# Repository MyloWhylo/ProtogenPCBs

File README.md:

# ProtogenPCBs
Repository for ProtoPico and BackpackController

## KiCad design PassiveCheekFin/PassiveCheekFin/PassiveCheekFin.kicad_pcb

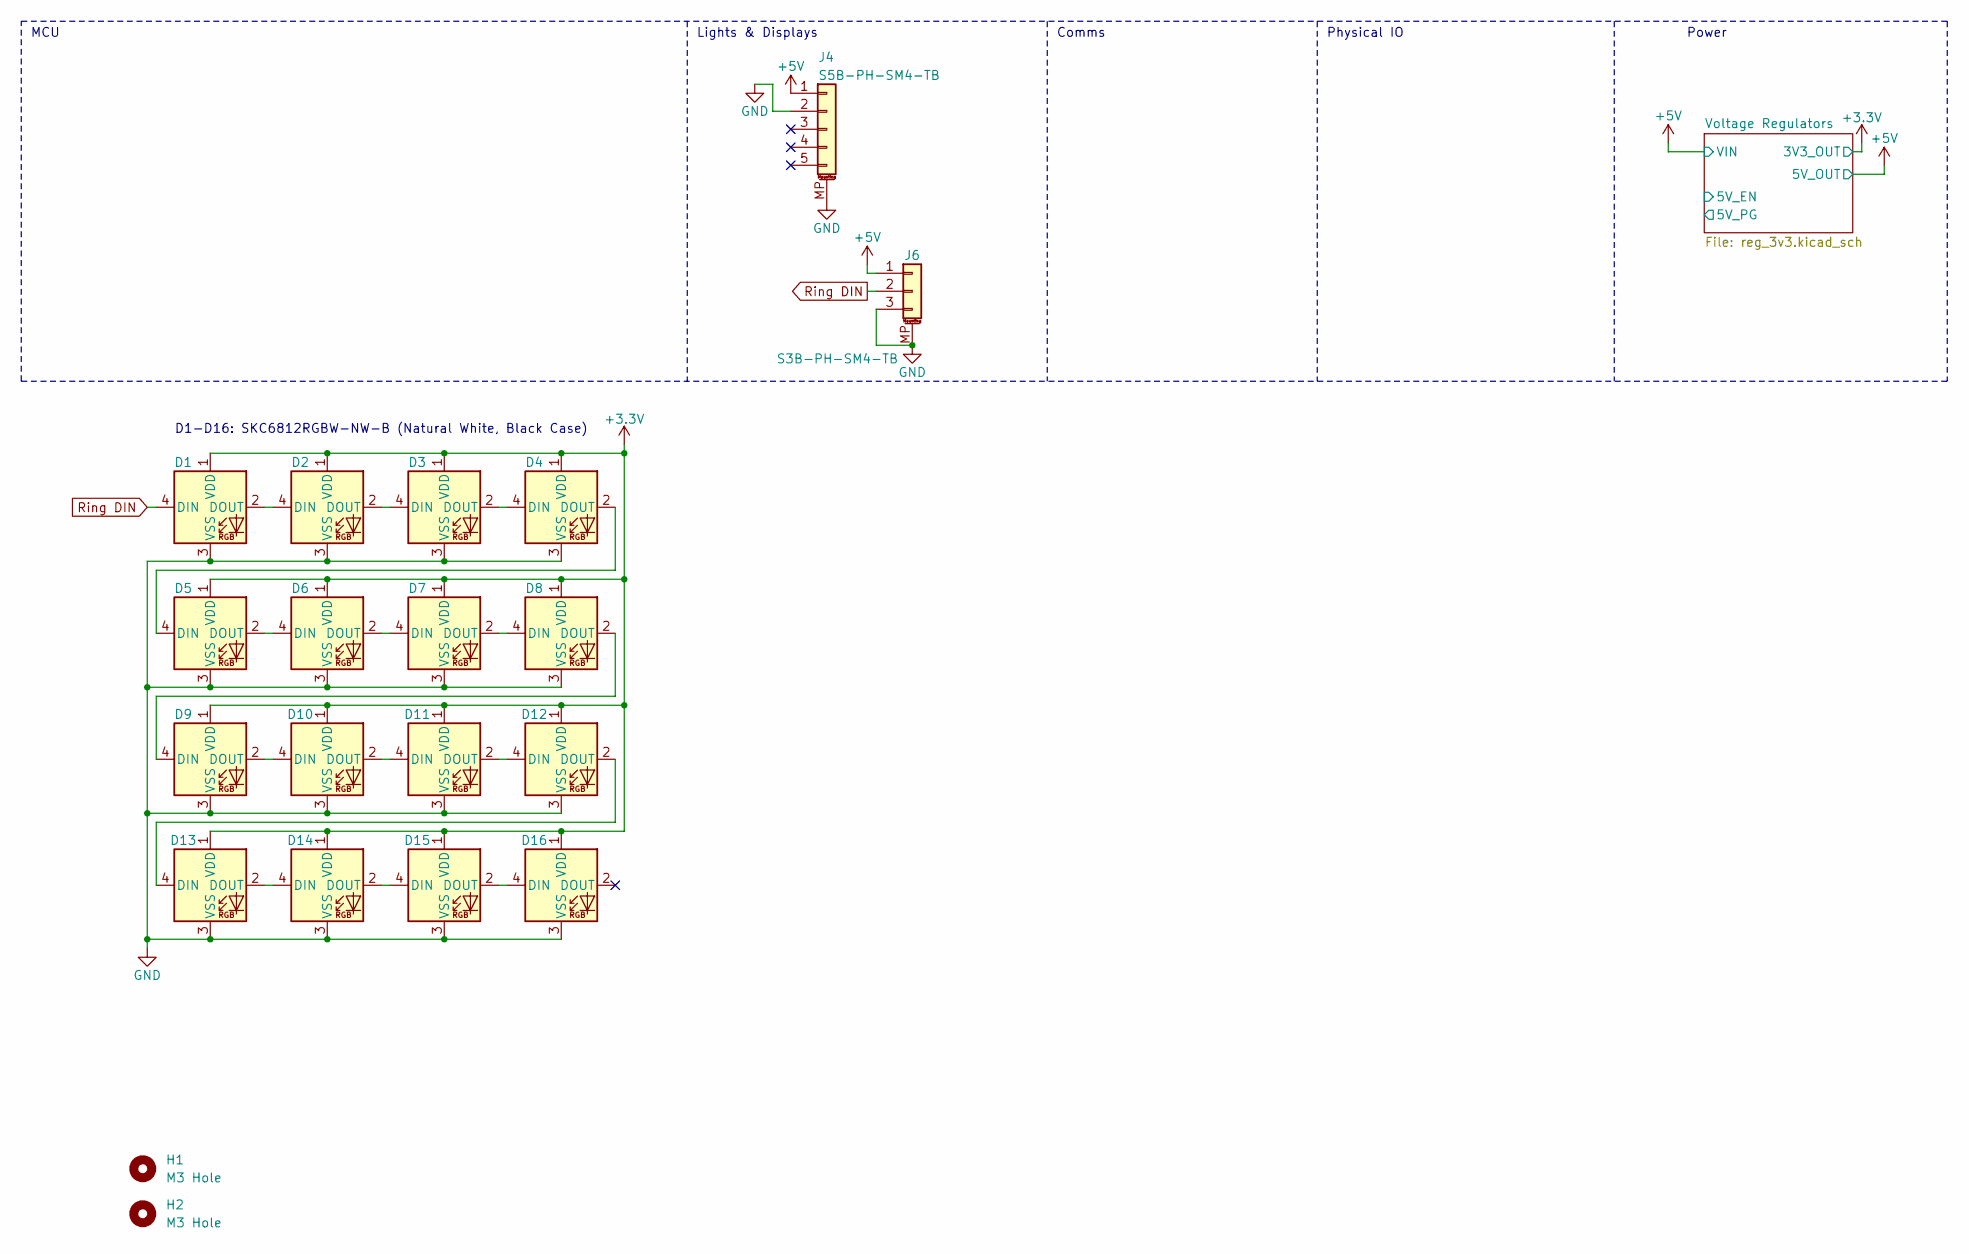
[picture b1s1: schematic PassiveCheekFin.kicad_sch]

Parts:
D1, D2, D3, D4, D5, D6, D7, D8, D9, D10, D11, D12, D13, D14, D15, D16: SKC6812RGBW-NW-B; LED_WS2812B_PLCC4_5.0x5.0mm_P3.2mm
H1, H2: M3 Hole; MountingHole_3.2mm_M3_ISO14580
J4: S5B-PH-SM4-TB; JST_PH_S5B-PH-SM4-TB_1x05-1MP_P2.00mm_Horizontal
J6: S3B-PH-SM4-TB; JST_PH_S3B-PH-SM4-TB_1x03-1MP_P2.00mm_Horizontal

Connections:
+3.3V: D1.1 (VDD), D2.1 (VDD), D3.1 (VDD), D4.1 (VDD), D5.1 (VDD), D6.1 (VDD), D7.1 (VDD), D8.1 (VDD), D9.1 (VDD), D10.1 (VDD), D11.1 (VDD), D12.1 (VDD), D13.1 (VDD), D14.1 (VDD), D15.1 (VDD), D16.1 (VDD); also elsewhere on the board
+5V: J4.1, J6.1; also elsewhere on the board
GND: D1.3 (VSS), D2.3 (VSS), D3.3 (VSS), D4.3 (VSS), D5.3 (VSS), D6.3 (VSS), D7.3 (VSS), D8.3 (VSS), D9.3 (VSS), D10.3 (VSS), D11.3 (VSS), D12.3 (VSS), D13.3 (VSS), D14.3 (VSS), D15.3 (VSS), D16.3 (VSS), J4.2, J4.MP (MountPin), J6.3, J6.MP (MountPin); also elsewhere on the board
unnamed: D1.2 (DOUT), D2.4 (DIN)
unnamed: D2.2 (DOUT), D3.4 (DIN)
unnamed: D3.2 (DOUT), D4.4 (DIN)
unnamed: D4.2 (DOUT), D5.4 (DIN)
unnamed: D5.2 (DOUT), D6.4 (DIN)
unnamed: D6.2 (DOUT), D7.4 (DIN)
unnamed: D7.2 (DOUT), D8.4 (DIN)
unnamed: D8.2 (DOUT), D9.4 (DIN)
unnamed: D9.2 (DOUT), D10.4 (DIN)
unnamed: D10.2 (DOUT), D11.4 (DIN)
unnamed: D11.2 (DOUT), D12.4 (DIN)
unnamed: D12.2 (DOUT), D13.4 (DIN)
unnamed: D13.2 (DOUT), D14.4 (DIN)
unnamed: D14.2 (DOUT), D15.4 (DIN)
unnamed: D15.2 (DOUT), D16.4 (DIN)
Ring DIN: D1.4 (DIN), J6.2

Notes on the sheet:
Power
Physical IO
Comms
Lights & Displays
MCU
D1-D16: SKC6812RGBW-NW-B (Natural White, Black Case)

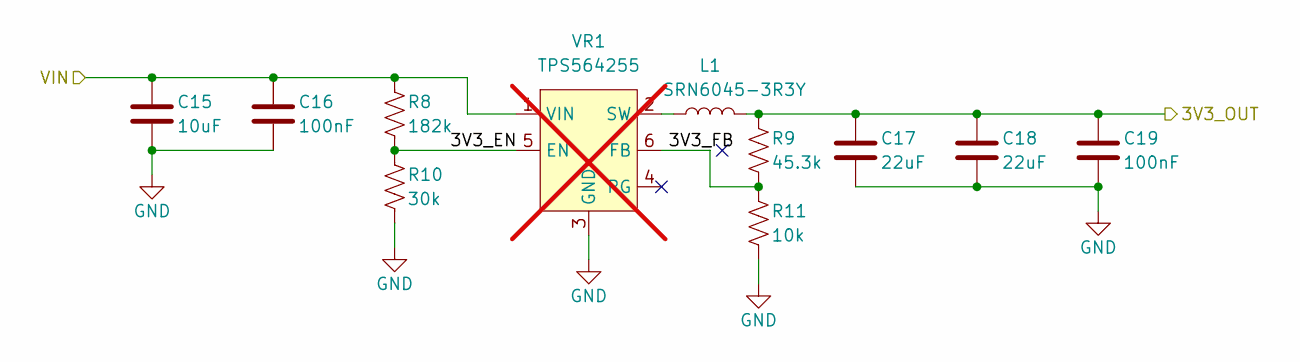
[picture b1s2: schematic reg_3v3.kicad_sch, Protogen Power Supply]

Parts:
C15: 10uF; C_0805_2012Metric
C16, C19: 100nF; C_0603_1608Metric
C17, C18: 22uF; C_0805_2012Metric
L1: SRN6045-3R3Y; L_Bourns-SRN6028
R8: 182k; R_0805_2012Metric_Pad1.20x1.40mm_HandSolder
R9: 45.3k; R_0402_1005Metric
R10: 30k; R_0805_2012Metric_Pad1.20x1.40mm_HandSolder
R11: 10k; R_0402_1005Metric
VR1: TPS564255; SOT-563; not fitted

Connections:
+3.3V: C17.1, C18.1, C19.1, L1.2, R9.1; also elsewhere on the board
+5V: C15.1, C16.1, R8.1, VR1.1 (VIN); also elsewhere on the board
/Voltage Regulators/3V3_EN: R8.2, R10.1, VR1.5 (EN)
/Voltage Regulators/3V3_FB: R9.2, R11.1, VR1.6 (FB)
GND: C15.2, C16.2, C17.2, C18.2, C19.2, R10.2, R11.2, VR1.3 (GND); also elsewhere on the board
unnamed: L1.1, VR1.2 (SW)

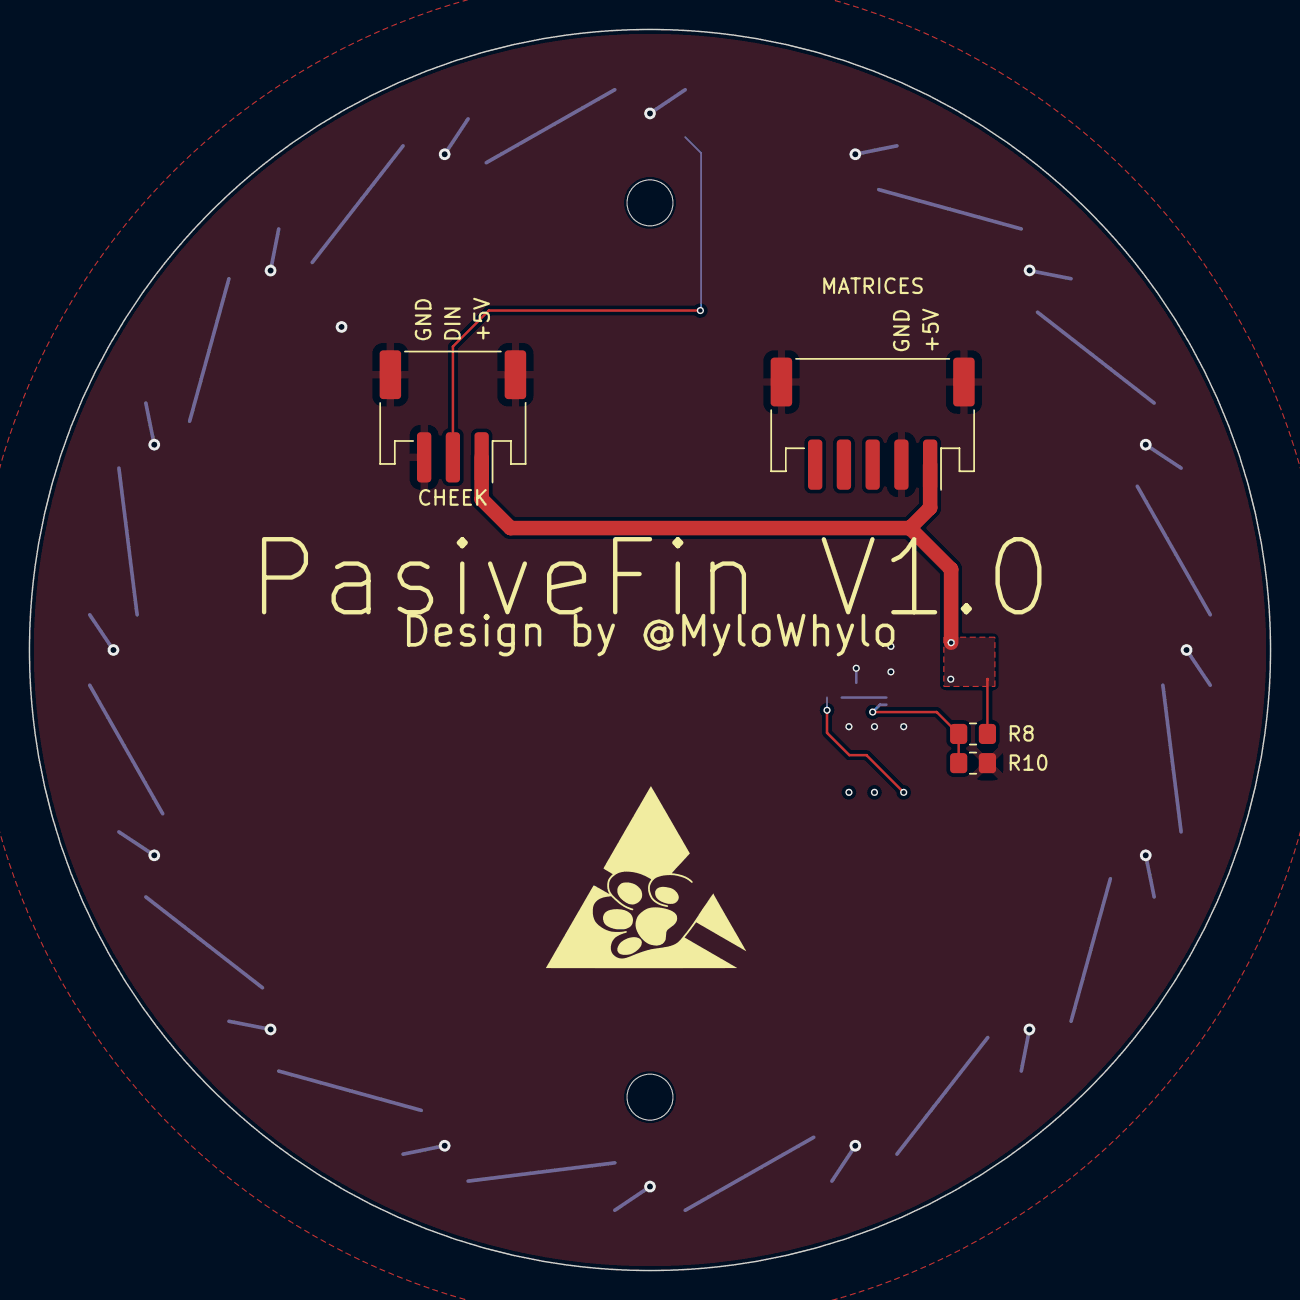
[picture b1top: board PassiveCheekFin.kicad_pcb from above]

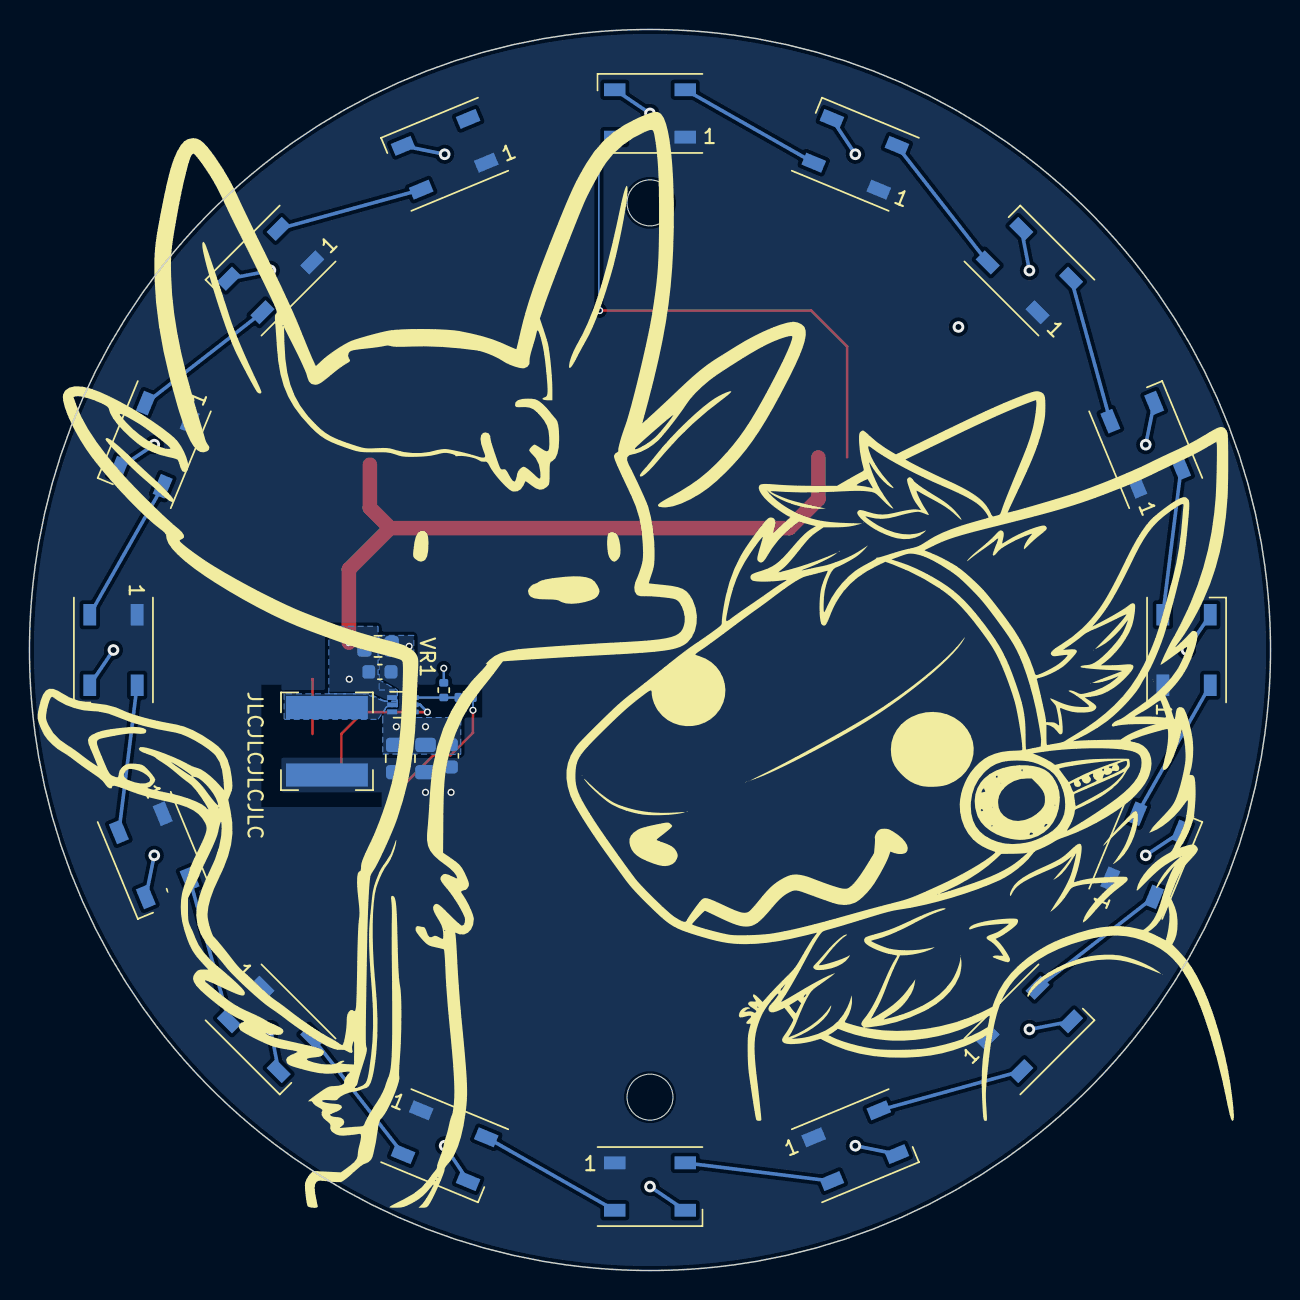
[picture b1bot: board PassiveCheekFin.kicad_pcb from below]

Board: 2 copper layers, 86.4 x 86.4 mm, 31 parts (27 on the bottom side), 22 nets.

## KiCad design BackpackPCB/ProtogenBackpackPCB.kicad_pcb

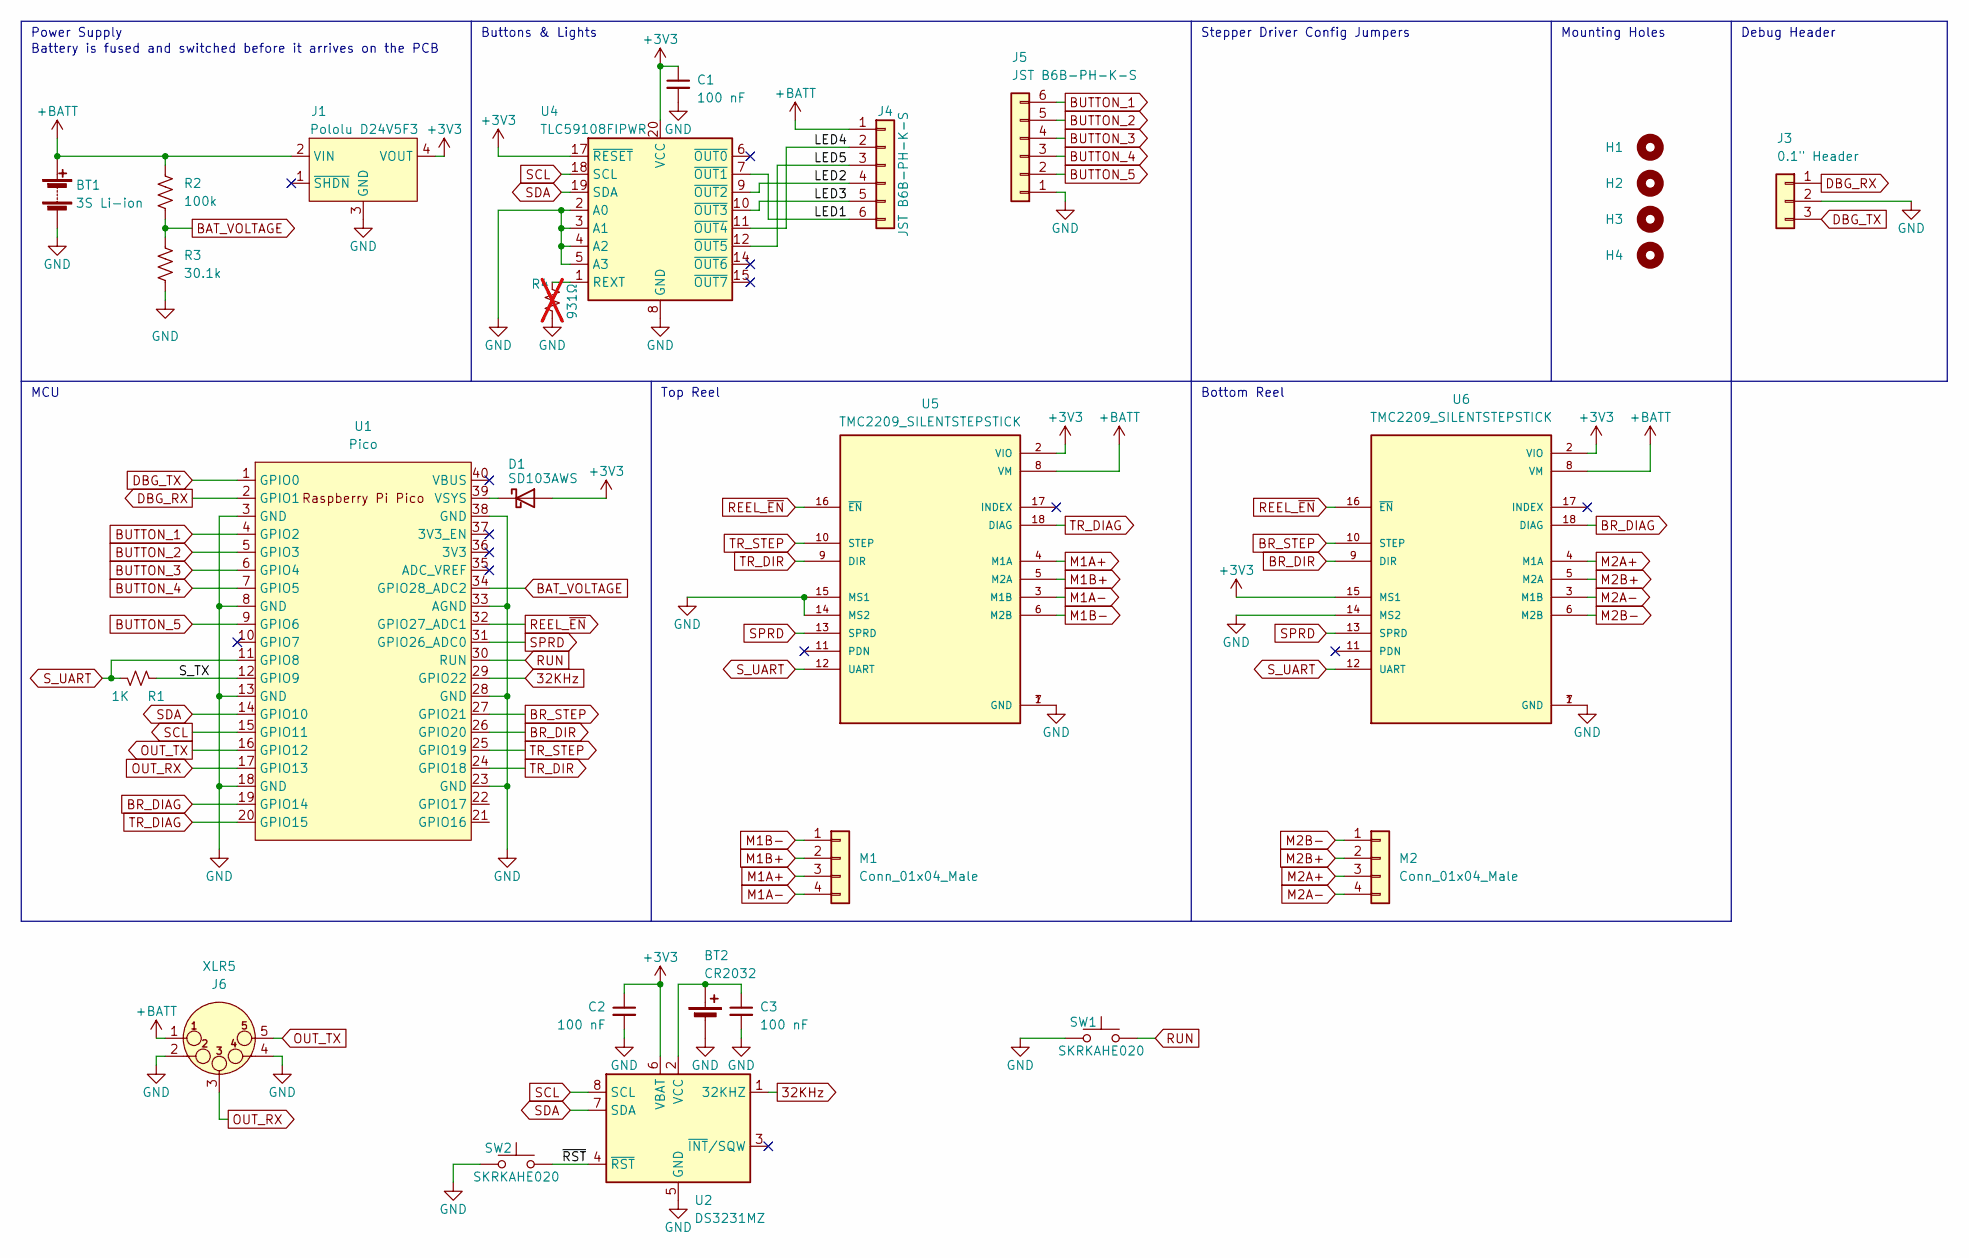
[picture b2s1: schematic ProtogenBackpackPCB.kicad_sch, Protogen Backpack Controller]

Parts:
BT1: 3S Li-ion; JST_XH_B2B-XH-AM_1x02_P2.50mm_Vertical
BT2: CR2032; BatteryHolder_Keystone_1060_1x2032
C1, C2, C3: 100 nF; C_0603_1608Metric_Pad1.08x0.95mm_HandSolder
D1: SD103AWS; D_SOD-323_HandSoldering
H1, H2, H3, H4: MountingHole_Pad; MountingHole_3.2mm_M3_ISO7380
J1: Pololu D24V5F3; Pololu_D24V5Fx
J3: 0.1" Header; PinSocket_1x03_P2.54mm_Vertical
J4, J5: JST B6B-PH-K-S; JST_PH_B6B-PH-K_1x06_P2.00mm_Vertical
J6: XLR5; JST_PH_B5B-PH-K_1x05_P2.00mm_Vertical
M1, M2: Conn_01x04_Male; JST_PH_B4B-PH-K_1x04_P2.00mm_Vertical
R1: 1K; R_0805_2012Metric_Pad1.20x1.40mm_HandSolder
R2: 100k; R_0603_1608Metric_Pad0.98x0.95mm_HandSolder
R3: 30.1k; R_0603_1608Metric_Pad0.98x0.95mm_HandSolder
R4: 931Ω; R_0402_1005Metric_Pad0.72x0.64mm_HandSolder; not fitted
SW1, SW2: SKRKAHE020; SW_Push_SPST_NO_Alps_SKRK
U1: Pico; RPi_Pico_SMD_TH
U2: DS3231MZ; SOIC-8_3.9x4.9mm_P1.27mm
U4: TLC59108FIPWR; TSSOP-20_4.4x6.5mm_P0.65mm
U5, U6: TMC2209_SILENTSTEPSTICK; MODULE_TMC2209_SILENTSTEPSTICK; PARTREV 1.20

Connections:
32KHz: U1.29 (GPIO22), U2.1 (32KHZ)
+3V3: C1.1, C2.1, D1.2 (A), J1.4 (VOUT), U2.6 (VBAT), U4.17 (~RESET), U4.20 (VCC), U5.2 (VIO), U6.2 (VIO), U6.15 (MS1)
+BATT: BT1.1 (+), J1.2 (VIN), J4.1, J6.1, R2.1, U5.8 (VM), U6.8 (VM)
/LED1: J4.6, U4.7 (~OUT1)
/LED2: J4.4, U4.9 (~OUT2)
/LED3: J4.5, U4.10 (~OUT3)
/LED4: J4.2, U4.11 (~OUT4)
/LED5: J4.3, U4.12 (~OUT5)
/S_TX: R1.2, U1.12 (GPIO9)
/~RST: SW2.2, U2.4 (~RST)
BAT_VOLTAGE: R2.2, R3.1, U1.34 (GPIO28_ADC2)
BR_DIAG: U1.19 (GPIO14), U6.18 (DIAG)
BR_DIR: U1.26 (GPIO20), U6.9 (DIR)
BR_STEP: U1.27 (GPIO21), U6.10 (STEP)
BUTTON_1: J5.6, U1.4 (GPIO2)
BUTTON_2: J5.5, U1.5 (GPIO3)
BUTTON_3: J5.4, U1.6 (GPIO4)
BUTTON_4: J5.3, U1.7 (GPIO5)
BUTTON_5: J5.2, U1.9 (GPIO6)
DBG_RX: J3.1, U1.2 (GPIO1)
DBG_TX: J3.3, U1.1 (GPIO0)
GND: BT1.2 (-), BT2.2 (-), C1.2, C2.2, C3.2, J1.3 (GND), J3.2, J5.1, J6.2, J6.4 (P3), R3.2, R4.1, SW1.1, SW2.1, U1.3 (GND), U1.8 (GND), U1.13 (GND), U1.18 (GND), U1.23 (GND), U1.28 (GND), U1.33 (AGND), U1.38 (GND), U2.5 (GND), U4.2 (A0), U4.3 (A1), U4.4 (A2), U4.5 (A3), U4.8 (GND), U4.13 (GND), U4.16 (GND), U5.1 (GND), U5.7 (GND), U5.14 (MS2), U5.15 (MS1), U6.1 (GND), U6.7 (GND), U6.14 (MS2)
M1A+: M1.3, U5.4 (M1A)
M1A-: M1.4, U5.3 (M1B)
M1B+: M1.2, U5.5 (M2A)
M1B-: M1.1, U5.6 (M2B)
M2A+: M2.3, U6.4 (M1A)
M2A-: M2.4, U6.3 (M1B)
M2B+: M2.2, U6.5 (M2A)
M2B-: M2.1, U6.6 (M2B)
unnamed: BT2.1 (+), C3.1, U2.2 (VCC)
unnamed: D1.1 (K), U1.39 (VSYS)
unnamed: R4.2, U4.1 (REXT)
OUT_RX: J6.3, U1.17 (GPIO13)
OUT_TX: J6.5, U1.16 (GPIO12)
REEL_~EN: U1.32 (GPIO27_ADC1), U5.16 (~EN), U6.16 (~EN)
RUN: SW1.2, U1.30 (RUN)
SCL: U1.15 (GPIO11), U2.8 (SCL), U4.18 (SCL)
SDA: U1.14 (GPIO10), U2.7 (SDA), U4.19 (SDA)
SPRD: U1.31 (GPIO26_ADC0), U5.13 (SPRD), U6.13 (SPRD)
S_UART: R1.1, U1.11 (GPIO8), U5.12 (UART), U6.12 (UART)
TR_DIAG: U1.20 (GPIO15), U5.18 (DIAG)
TR_DIR: U1.24 (GPIO18), U5.9 (DIR)
TR_STEP: U1.25 (GPIO19), U5.10 (STEP)

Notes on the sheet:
Battery is fused and switched before it arrives on the PCB
Stepper Driver Config Jumpers
Power Supply
Buttons & Lights
Debug Header
Top Reel
Mounting Holes
MCU
Bottom Reel

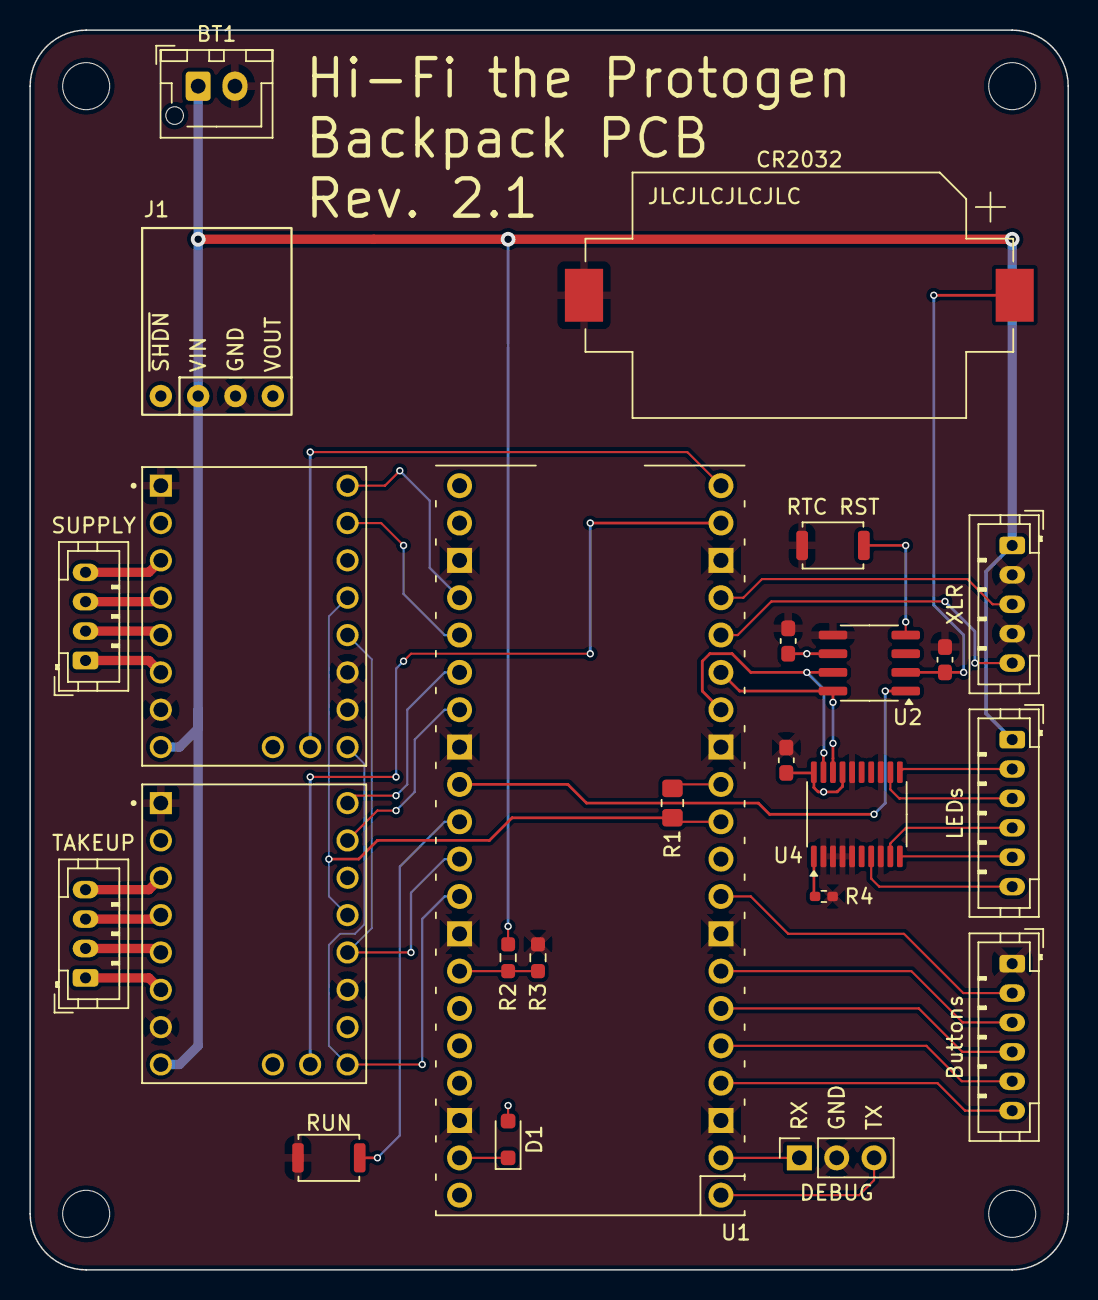
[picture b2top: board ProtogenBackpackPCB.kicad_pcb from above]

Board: 2 copper layers, 70.6 x 84.3 mm, 28 parts (0 on the bottom side), 44 nets.

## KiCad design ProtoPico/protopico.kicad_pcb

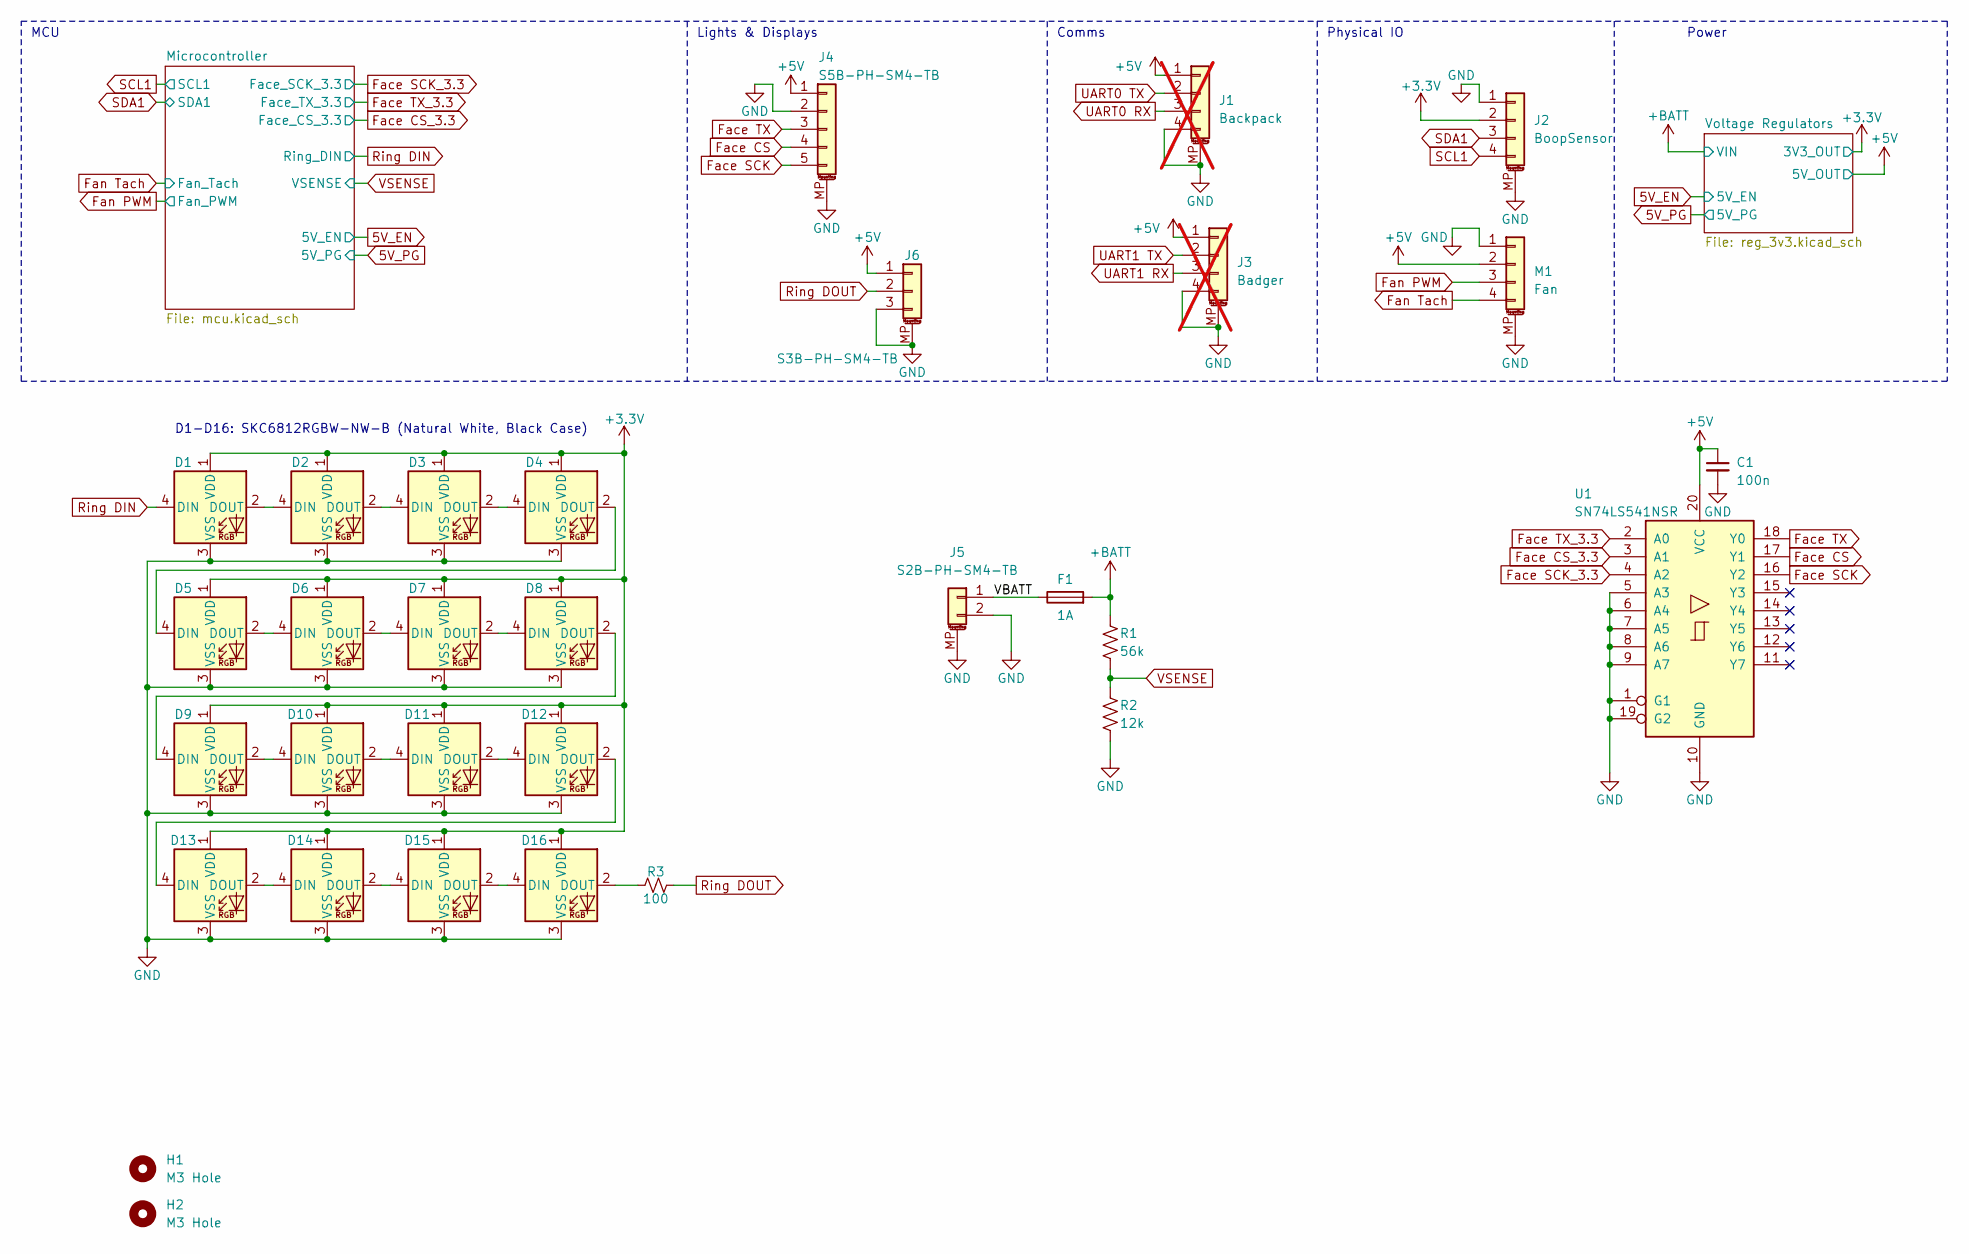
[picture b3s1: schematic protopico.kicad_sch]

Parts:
C1: 100n; C_0402_1005Metric
D1, D2, D3, D4, D5, D6, D7, D8, D9, D10, D11, D12, D13, D14, D15, D16: SKC6812RGBW-NW-B; LED_WS2812B_PLCC4_5.0x5.0mm_P3.2mm
F1: 1A; Fuse_1206_3216Metric_Pad1.42x1.75mm_HandSolder
H1, H2: M3 Hole; MountingHole_3.2mm_M3_ISO14580
J1: Backpack; JST_SH_SM04B-SRSS-TB_1x04-1MP_P1.00mm_Horizontal; not fitted
J2: BoopSensor; JST_GH_SM04B-GHS-TB_1x04-1MP_P1.25mm_Horizontal
J3: Badger; JST_SH_SM04B-SRSS-TB_1x04-1MP_P1.00mm_Horizontal; not fitted
J4: S5B-PH-SM4-TB; JST_PH_S5B-PH-SM4-TB_1x05-1MP_P2.00mm_Horizontal
J5: S2B-PH-SM4-TB; JST_PH_S2B-PH-SM4-TB_1x02-1MP_P2.00mm_Horizontal
J6: S3B-PH-SM4-TB; JST_PH_S3B-PH-SM4-TB_1x03-1MP_P2.00mm_Horizontal
M1: Fan; JST_GH_SM04B-GHS-TB_1x04-1MP_P1.25mm_Horizontal
R1: 56k; R_0805_2012Metric_Pad1.20x1.40mm_HandSolder
R2: 12k; R_0805_2012Metric_Pad1.20x1.40mm_HandSolder
R3: 100; R_0402_1005Metric
U1: SN74LS541NSR; TSSOP-20_4.4x6.5mm_P0.65mm

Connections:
+3.3V: D1.1 (VDD), D2.1 (VDD), D3.1 (VDD), D4.1 (VDD), D5.1 (VDD), D6.1 (VDD), D7.1 (VDD), D8.1 (VDD), D9.1 (VDD), D10.1 (VDD), D11.1 (VDD), D12.1 (VDD), D13.1 (VDD), D14.1 (VDD), D15.1 (VDD), D16.1 (VDD), J2.2; also elsewhere on the board
+5V: C1.1, J1.1, J3.1, J4.1, J6.1, M1.2, U1.20 (VCC); also elsewhere on the board
+BATT: F1.2, R1.1; also elsewhere on the board
/VBATT: F1.1, J5.1
Face CS: J4.4, U1.17 (Y1)
Face CS_3.3: U1.3 (A1); also elsewhere on the board
Face SCK: J4.5, U1.16 (Y2)
Face SCK_3.3: U1.4 (A2); also elsewhere on the board
Face TX: J4.3, U1.18 (Y0)
Face TX_3.3: U1.2 (A0); also elsewhere on the board
Fan PWM: M1.3; also elsewhere on the board
Fan Tach: M1.4; also elsewhere on the board
GND: C1.2, D1.3 (VSS), D2.3 (VSS), D3.3 (VSS), D4.3 (VSS), D5.3 (VSS), D6.3 (VSS), D7.3 (VSS), D8.3 (VSS), D9.3 (VSS), D10.3 (VSS), D11.3 (VSS), D12.3 (VSS), D13.3 (VSS), D14.3 (VSS), D15.3 (VSS), D16.3 (VSS), J1.4, J1.MP (MountPin), J2.1, J2.MP (MountPin), J3.4, J3.MP (MountPin), J4.2, J4.MP (MountPin), J5.2, J5.MP (MountPin), J6.3, J6.MP (MountPin), M1.1, M1.MP (MountPin), R2.2, U1.1 (G1), U1.5 (A3), U1.6 (A4), U1.7 (A5), U1.8 (A6), U1.9 (A7), U1.10 (GND), U1.19 (G2); also elsewhere on the board
unnamed: D1.2 (DOUT), D2.4 (DIN)
unnamed: D2.2 (DOUT), D3.4 (DIN)
unnamed: D3.2 (DOUT), D4.4 (DIN)
unnamed: D4.2 (DOUT), D5.4 (DIN)
unnamed: D5.2 (DOUT), D6.4 (DIN)
unnamed: D6.2 (DOUT), D7.4 (DIN)
unnamed: D7.2 (DOUT), D8.4 (DIN)
unnamed: D8.2 (DOUT), D9.4 (DIN)
unnamed: D9.2 (DOUT), D10.4 (DIN)
unnamed: D10.2 (DOUT), D11.4 (DIN)
unnamed: D11.2 (DOUT), D12.4 (DIN)
unnamed: D12.2 (DOUT), D13.4 (DIN)
unnamed: D13.2 (DOUT), D14.4 (DIN)
unnamed: D14.2 (DOUT), D15.4 (DIN)
unnamed: D15.2 (DOUT), D16.4 (DIN)
unnamed: D16.2 (DOUT), R3.1
Ring DIN: D1.4 (DIN); also elsewhere on the board
Ring DOUT: J6.2, R3.2
SCL1: J2.4; also elsewhere on the board
SDA1: J2.3; also elsewhere on the board
VSENSE: R1.2, R2.1; also elsewhere on the board

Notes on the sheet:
Power
Physical IO
Comms
Lights & Displays
MCU
D1-D16: SKC6812RGBW-NW-B (Natural White, Black Case)

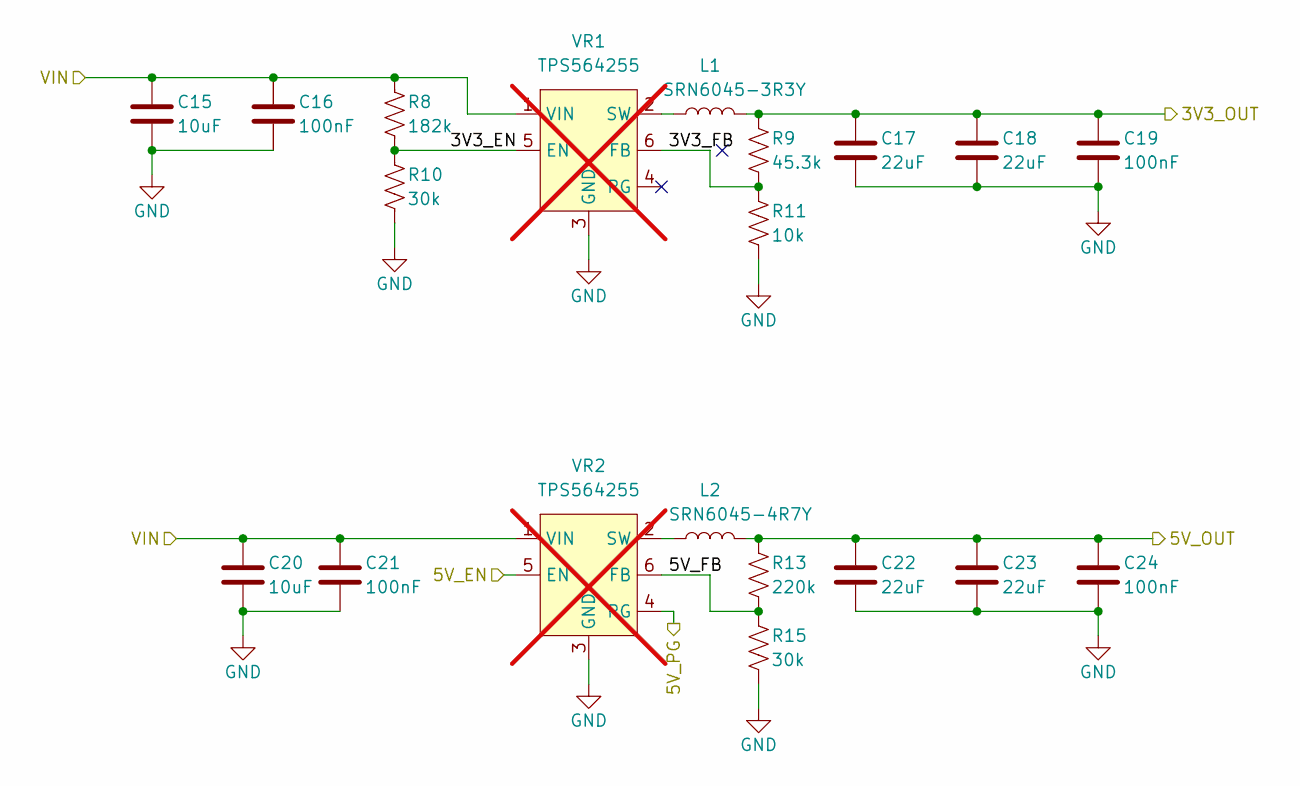
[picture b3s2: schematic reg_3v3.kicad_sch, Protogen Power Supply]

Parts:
C15, C20: 10uF; C_0805_2012Metric
C16, C19, C21, C24: 100nF; C_0603_1608Metric
C17, C18, C22, C23: 22uF; C_0805_2012Metric
L1: SRN6045-3R3Y; L_Bourns-SRN6028
L2: SRN6045-4R7Y; L_Bourns-SRN6028
R8: 182k; R_0805_2012Metric_Pad1.20x1.40mm_HandSolder
R9: 45.3k; R_0402_1005Metric
R10: 30k; R_0805_2012Metric_Pad1.20x1.40mm_HandSolder
R11: 10k; R_0402_1005Metric
R13: 220k; R_0402_1005Metric
R15: 30k; R_0402_1005Metric
VR1, VR2: TPS564255; SOT-563; not fitted

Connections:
5V_EN: VR2.5 (EN); also elsewhere on the board
5V_PG: VR2.4 (PG); also elsewhere on the board
+3.3V: C17.1, C18.1, C19.1, L1.2, R9.1; also elsewhere on the board
+5V: C22.1, C23.1, C24.1, L2.2, R13.1; also elsewhere on the board
+BATT: C15.1, C16.1, C20.1, C21.1, R8.1, VR1.1 (VIN), VR2.1 (VIN); also elsewhere on the board
/Voltage Regulators/3V3_EN: R8.2, R10.1, VR1.5 (EN)
/Voltage Regulators/3V3_FB: R9.2, R11.1, VR1.6 (FB)
/Voltage Regulators/5V_FB: R13.2, R15.1, VR2.6 (FB)
GND: C15.2, C16.2, C17.2, C18.2, C19.2, C20.2, C21.2, C22.2, C23.2, C24.2, R10.2, R11.2, R15.2, VR1.3 (GND), VR2.3 (GND); also elsewhere on the board
unnamed: L1.1, VR1.2 (SW)
unnamed: L2.1, VR2.2 (SW)
